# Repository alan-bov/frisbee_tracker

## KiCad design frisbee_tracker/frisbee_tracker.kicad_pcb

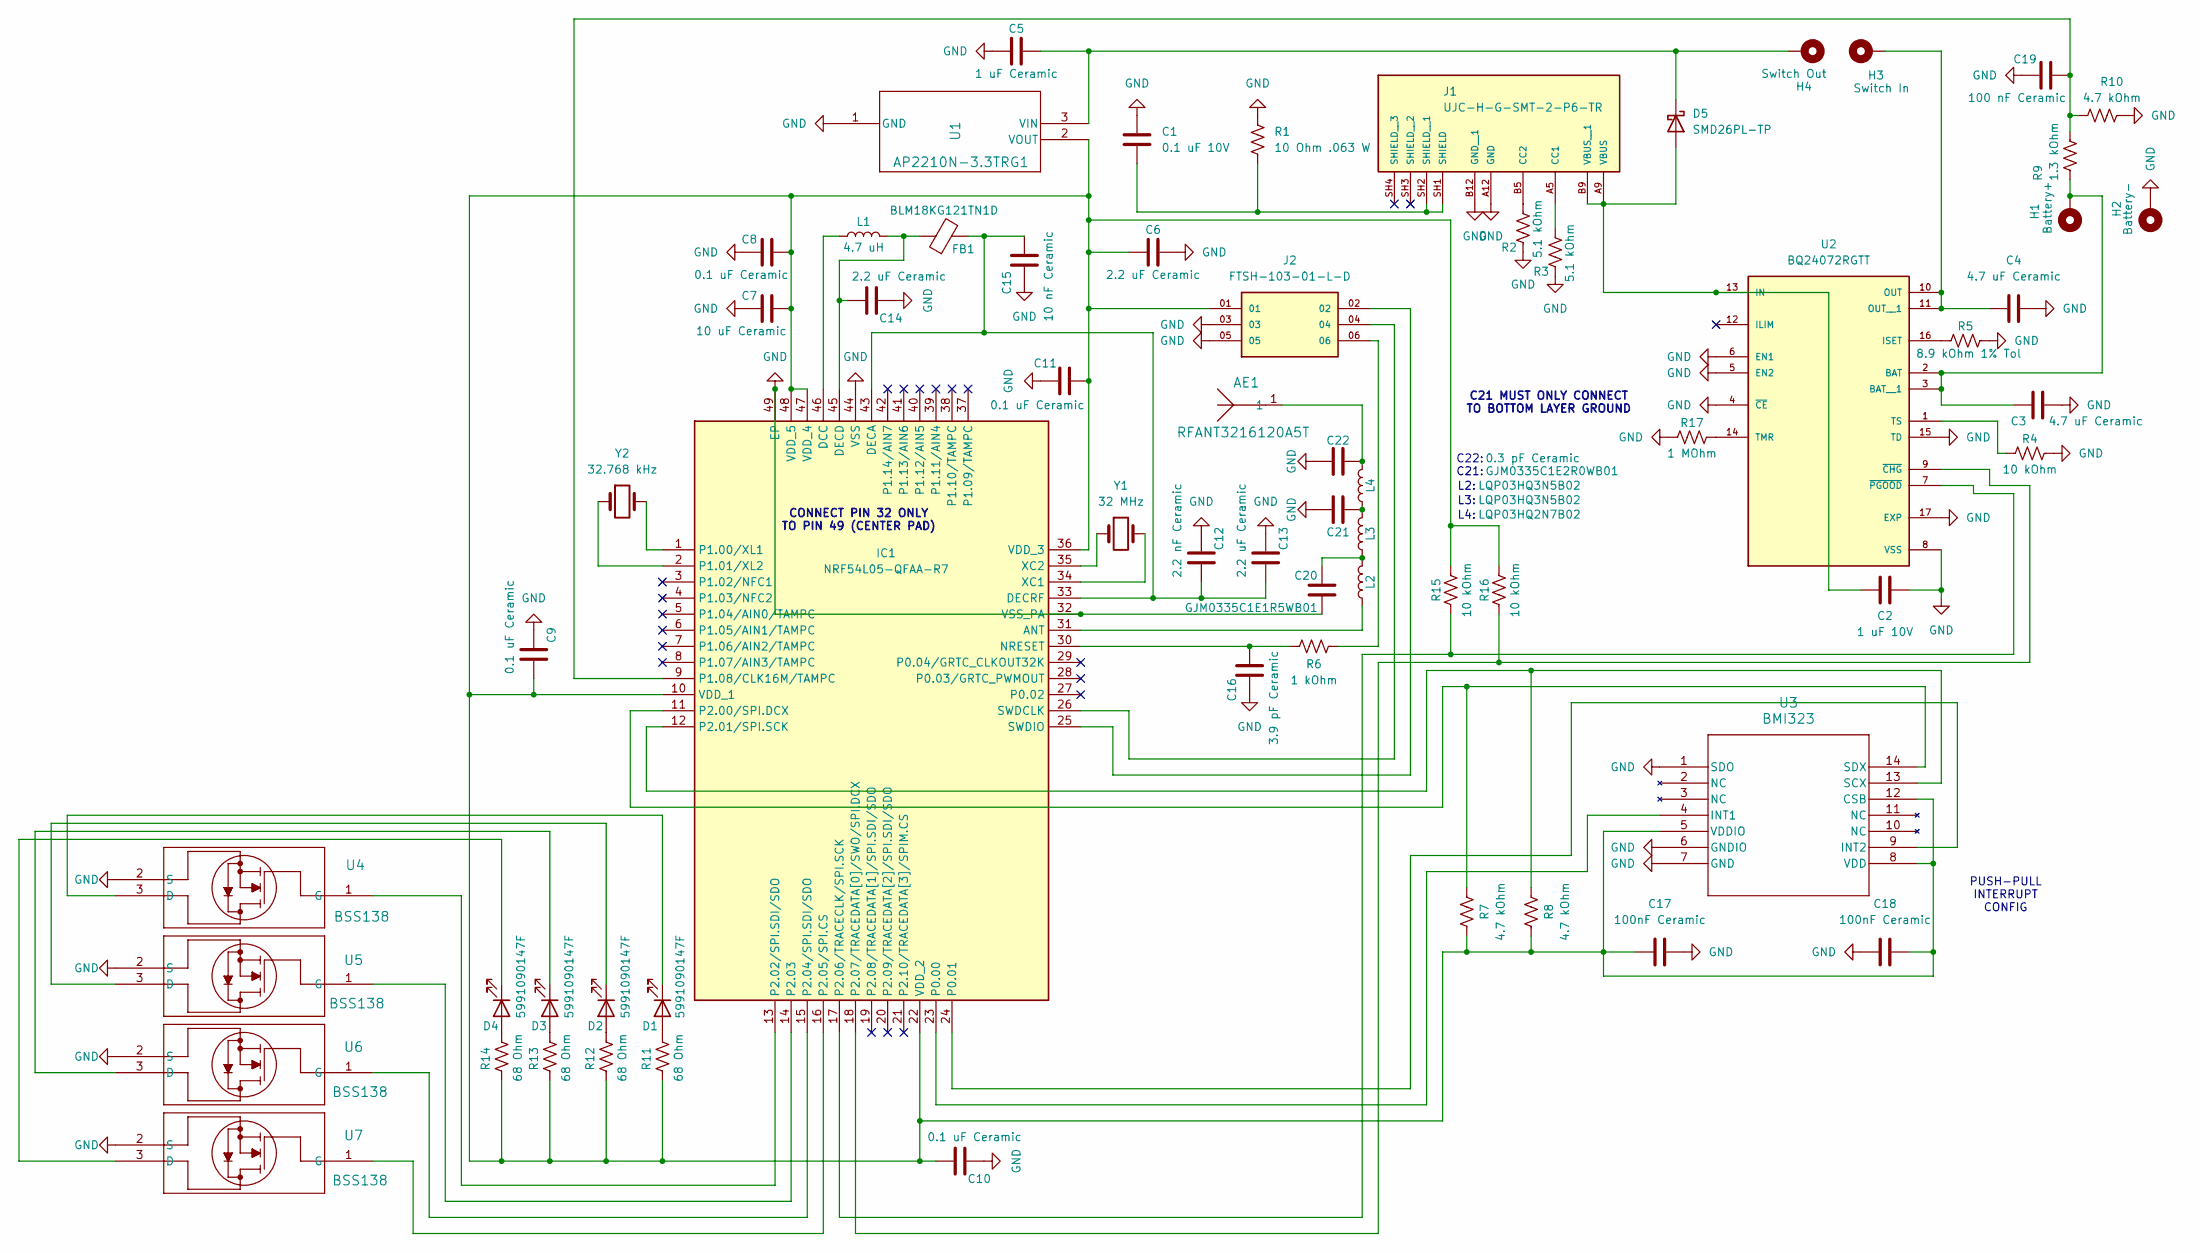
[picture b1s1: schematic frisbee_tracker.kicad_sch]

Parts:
AE1: RFANT3216120A5T
C1: 0.1 uF 10V; C_0603_1608Metric
C2: 1 uF 10V; C_0603_1608Metric
C3, C4: 4.7 uF Ceramic; C_0603_1608Metric
C5: 1 uF Ceramic; C_0603_1608Metric
C6, C13, C14: 2.2 uF Ceramic; C_0603_1608Metric
C7: 10 uF Ceramic; C_0603_1608Metric
C8, C9, C10, C11: 0.1 uF Ceramic; C_0603_1608Metric
C12: 2.2 nF Ceramic; C_0603_1608Metric
C15: 10 nF Ceramic; C_0603_1608Metric
C16: 3.9 pF Ceramic; C_0603_1608Metric
C17, C18: 100nF Ceramic; C_0603_1608Metric
C19: 100 nF Ceramic; C_0603_1608Metric
C20: GJM0335C1E1R5WB01; C_0201_0603Metric
C21: GJM0335C1E2R0WB01; C_0201_0603Metric
C22: 0.3 pF Ceramic; C_0603_1608Metric
D1, D2, D3, D4: 5991090147F; LED_0603_1608Metric
D5: SMD26PL-TP
FB1: BLM18KG121TN1D
H1: Battery+; PinHeader_1x01_P1.27mm_Vertical
H2: Battery-; PinHeader_1x01_P1.27mm_Vertical
H3: Switch In; PinHeader_1x01_P1.27mm_Vertical
H4: Switch Out; PinHeader_1x01_P1.27mm_Vertical
IC1: NRF54L05-QFAA-R7; Mouser Part Number 949-NRF54L05-QFAA-R7
J1: UJC-H-G-SMT-2-P6-TR; PARTREV 1.0
J2: FTSH-103-01-L-D; PARTREV B
L1: 4.7 uH; L_0603_1608Metric
L2: LQP03HQ2N7B02; LQP03HQ2N7B02D
L3, L4: LQP03HQ3N5B02; LQP03HQ3N5B02D
R1: 10 Ohm .063 W; R_0603_1608Metric
R2, R3: 5.1 kOhm; R_0603_1608Metric
R4, R15, R16: 10 kOhm; R_0603_1608Metric
R5: 8.9 kOhm 1% Tol; R_0603_1608Metric
R6: 1 kOhm; R_0603_1608Metric
R7, R8, R10: 4.7 kOhm; R_0603_1608Metric
R9: 1.3 kOhm; R_0603_1608Metric
R11, R12, R13, R14: 68 Ohm; R_0603_1608Metric
R17: 1 MOhm; R_0603_1608Metric
U1: AP2210N-3.3TRG1
U2: BQ24072RGTT; PARTREV N
U3: BMI323
U4, U5, U6, U7: BSS138
Y1: 32 MHz; ECS-320-8-37B2-JTY-TR
Y2: 32.768 kHz; Q 0,032768-JTX210-7-20-T1-HMR-70K-LF

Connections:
unnamed: AE1.1, C22.2, L4.2
unnamed: C20.2, L2.2, L3.1
unnamed: C21.1, L3.2, L4.1
unnamed: D1.2 (A), R11.1
unnamed: D1.1 (K), U4.3 (D)
unnamed: D2.2 (A), R12.1
unnamed: D2.1 (K), U5.3 (D)
unnamed: D3.2 (A), R13.1
unnamed: D3.1 (K), U6.3 (D)
unnamed: D4.2 (A), R14.1
unnamed: D4.1 (K), U7.3 (D)
unnamed: C2.1, D5.2 (A), J1.A9 (VBUS), J1.B9 (VBUS__1), U2.13 (IN)
unnamed 12: C5.2, D5.1 (K), H4.1, U1.3 (VIN); also elsewhere on the board
unnamed: IC1.31 (ANT), L2.1
unnamed: IC1.46 (DCC), L1.1
unnamed: C12.2, C13.2, C15.2, FB1.2, IC1.33 (DECRF), IC1.43 (DECA)
unnamed: C14.2, FB1.1, IC1.45 (DECD), L1.2
unnamed: C16.2, IC1.30 (NRESET), R6.1
unnamed: IC1.23 (P0.00), U3.4 (INT1)
unnamed: IC1.24 (P0.01), U3.9 (INT2)
unnamed: IC1.1 (P1.00/XL1), Y2.2
unnamed: IC1.2 (P1.01/XL2), Y2.1
unnamed: C19.2, IC1.9 (P1.08/CLK16M/TAMPC), R9.1, R10.1
unnamed: IC1.11 (P2.00/SPI.DCX), R7.2, U3.14 (SDX)
unnamed: IC1.12 (P2.01/SPI.SCK), R8.2, U3.13 (SCX)
unnamed: IC1.13 (P2.02/SPI.SDI/SDO), U4.1 (G)
unnamed: IC1.14 (P2.03), U5.1 (G)
unnamed: IC1.15 (P2.04/SPI.SDI/SDO), U6.1 (G)
unnamed: IC1.16 (P2.05/SPI.CS), U7.1 (G)
unnamed: IC1.17 (P2.06/TRACECLK/SPI.SCK), R15.1, U2.7 (~PGOOD)
unnamed: IC1.18 (P2.07/TRACEDATA[0]/SWO/SPI.DCX), R16.1, U2.9 (~CHG)
unnamed: IC1.26 (SWDCLK), J2.04
unnamed: IC1.25 (SWDIO), J2.02
unnamed: C6.1, C7.2, C8.2, C9.2, C10.2, C11.2, C17.1, C18.2, IC1.10 (VDD_1), IC1.22 (VDD_2), IC1.36 (VDD_3), IC1.47 (VDD_4), IC1.48 (VDD_5), J2.01, R7.1, R8.1, R11.2, R12.2, R13.2, R14.2, R15.2, R16.2, U1.2 (VOUT), U3.5 (VDDIO), U3.8 (VDD), U3.12 (CSB)
unnamed: IC1.35 (XC2), Y1.1
unnamed: J1.A5 (CC1), R3.1
unnamed: J1.B5 (CC2), R2.1
unnamed: C1.2, J1.SH1 (SHIELD), J1.SH2 (SHIELD__1), R1.2
unnamed: J2.06, R6.2
unnamed 39: C3.1, H1.1, R9.2, U2.2 (BAT), U2.3 (BAT__1); also elsewhere on the board
unnamed: R5.1, U2.16 (ISET)
unnamed 41: C4.1, H3.1, U2.10 (OUT), U2.11 (OUT__1); also elsewhere on the board
unnamed: R17.2, U2.14 (TMR)
unnamed: R4.1, U2.1 (TS)

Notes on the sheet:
C21:
CONNECT PIN 32 ONLY TO PIN 49 (CENTER PAD)
L3:
C21 MUST ONLY CONNECT TO BOTTOM LAYER GROUND
L4:
C22:
L2:
PUSH-PULL INTERRUPT CONFIG

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
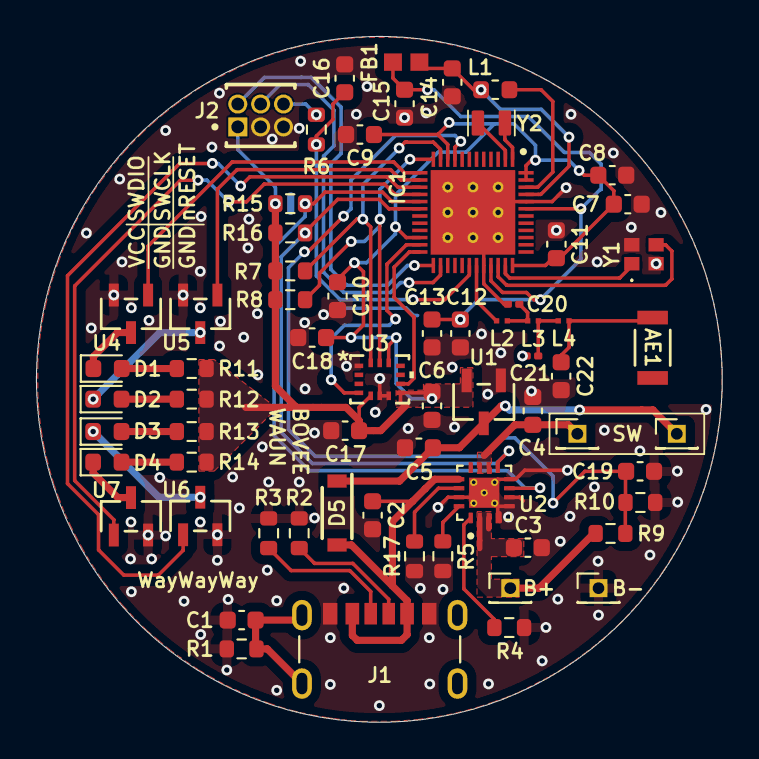
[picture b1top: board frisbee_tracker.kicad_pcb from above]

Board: 2 copper layers, 38.1 x 38.1 mm, 66 parts (0 on the bottom side), 46 nets.

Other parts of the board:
B+: Battery+; PinHeader_1x01_P1.27mm_Vertical
B-: Battery-; PinHeader_1x01_P1.27mm_Vertical
SW: Switch Out; PinHeader_1x01_P1.27mm_Vertical
SW#2: Switch In; PinHeader_1x01_P1.27mm_Vertical

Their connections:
unnamed 12: SW.1; also elsewhere on the board
unnamed 39: B+.1; also elsewhere on the board
unnamed 41: SW#2.1; also elsewhere on the board

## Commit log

2025-10-23 started schematic design
2025-10-24 Rough draft of schematic complete
2025-10-27 start of PCB design
2025-10-28 PCB design 75 percent complete
2025-10-29 rework on controller PCB wiring started
2025-10-30 PCB rework of MCU
2025-10-31 PCB design 90% complete
2025-11-03 Rough draft of PCB completed
2025-11-05 Added switch and Shottky diode to schematic
2025-11-05 PCB design complete and Gerbers generated
2025-11-06 firmware program created
